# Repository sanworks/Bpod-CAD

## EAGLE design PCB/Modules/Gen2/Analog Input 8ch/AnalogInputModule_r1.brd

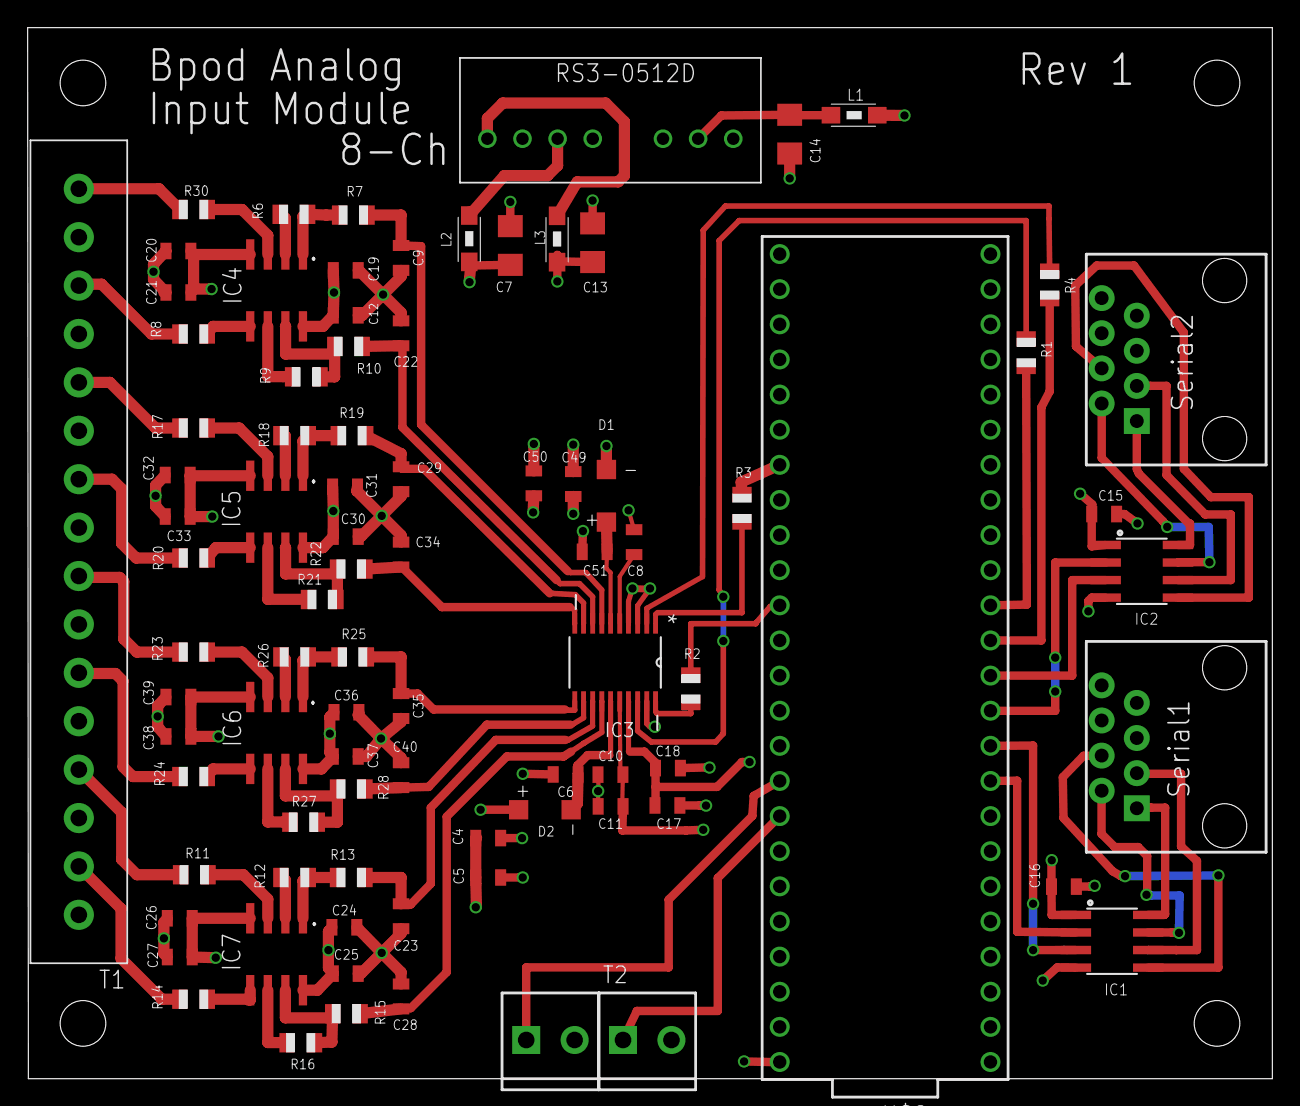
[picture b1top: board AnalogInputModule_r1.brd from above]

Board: 4 copper layers, 90.0 x 76.0 mm, 92 parts (0 on the bottom side), 74 nets.

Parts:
C4, C11, C12, C17, C21, C24, C27, C30, C33, C36, C39, C49: 10uF; 0805
C5, C6, C10, C15, C16, C18, C19, C20, C25, C26, C31, C32, C37, C38, C50, C51: 0.1uF; 0805
C7, C13, C14: 4.7uF; 1206
C8: 680nF; 0805
C9, C22, C23, C28, C29, C34, C35, C40: 2.7nF; 0805
D1, D2: MBR0520LT; SOD123
IC1, IC2: SN65HVD31DR; SO08
IC3: AD7327BRUZ; SOP65P640X120-20N
IC4, IC5, IC6, IC7: AD8599R; SO8
J9, J10: SCREWTERMINAL-3.5MM-2
L1, L2, L3: 1206
R1, R2, R3, R4: 22; R0805
R6, R8, R9, R11, R12, R14, R16, R17, R18, R20, R21, R23, R24, R26, R27, R30: 47; R0805
R7, R10, R13, R15, R19, R22, R25, R28: 180; R0805
RS3-0512D: RS3-0515D
T1: 16POS_SCREWTERMINAL
U$2, U$3: RJ45-8PTH; RJ45-8
U$4: GNDPLANESHRT
U$5, U$6, U$7, U$8: STAND-OFF
U$9: TEENSY_3.6_DIL

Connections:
+VOUT: L2.1, RS3-0512D.+VOUT
-VOUT: L3.1, RS3-0512D.-VOUT
ADC_CS: IC3.1, R3.1
AGND: C4.2, C5.2, C6.2, C8.1, C9.2, C10.2, C11.2, C12.2, C19.2, C20.2, C21.2, C22.2, C23.2, C24.2, C25.2, C26.2, C27.2, C28.2, C29.2, C30.2, C31.2, C32.2, C33.2, C34.2, C35.2, C36.2, C37.2, C38.2, C39.2, C40.2, C49.2, C50.2, C51.2, IC3.4, T1.P$1, T1.P$3, T1.P$5, T1.P$7, T1.P$9, T1.P$11, T1.P$13, T1.P$15, U$4.AGND, U$9.AGND
AIN0: R30.1, T1.P$16
AIN1: R8.1, T1.P$14
AIN2: R11.1, T1.P$4
AIN3: R14.1, T1.P$2
AIN4: R17.1, T1.P$12
AIN5: R20.1, T1.P$10
AIN6: R23.1, T1.P$8
AIN7: R24.1, T1.P$6
DGND: C7.2, C13.1, C14.2, C15.2, C16.2, C17.2, C18.2, IC1.4, IC2.4, IC3.3, IC3.19, J9.2, J10.2, RS3-0512D.-VIN, RS3-0512D.COM, U$4.GND, U$9.GND, U$9.GND1
MISO: IC3.18, R1.1
MOSI: IC3.2, R4.1
unnamed: IC1.6, U$2.3
unnamed: IC1.8, U$2.1
unnamed: IC1.5, U$2.4
unnamed: IC1.7, U$2.2
unnamed: IC2.6, U$3.3
unnamed: IC2.5, U$3.4
unnamed: IC2.8, U$3.1
unnamed: IC2.7, U$3.2
unnamed: R4.2, U$9.11
unnamed: R1.2, U$9.12
unnamed: C14.1, L1.2, RS3-0512D.+VIN
unnamed: R3.2, U$9.39/A20
unnamed: IC4.3, R30.2
unnamed: R2.2, U$9.13
unnamed: IC4.2, R6.1
unnamed: IC4.1, R6.2, R7.1
unnamed: J9.1, U$9.18/A4
unnamed: J10.1, U$9.19/A5
unnamed: IC4.5, R8.2
unnamed: IC4.6, R9.1
unnamed: IC4.7, R9.2, R10.1
unnamed: IC7.3, R11.2
unnamed: IC7.2, R12.1
unnamed: IC7.1, R12.2, R13.1
unnamed: IC7.5, R14.2
unnamed: IC7.6, R16.1
unnamed: IC7.7, R15.1, R16.2
unnamed: IC5.3, R17.2
unnamed: IC5.2, R18.1
unnamed: IC5.1, R18.2, R19.1
unnamed: IC5.5, R20.2
unnamed: IC5.6, R21.1
unnamed: IC5.7, R21.2, R22.1
unnamed: IC6.3, R23.2
unnamed: IC6.2, R26.1
unnamed: IC6.1, R25.1, R26.2
unnamed: IC6.5, R24.2
unnamed: IC6.6, R27.1
unnamed: IC6.7, R27.2, R28.1
REF: C8.2, IC3.5
RX1: IC1.2, U$9.7
RX2: IC2.2, U$9.9
SCLK: IC3.20, R2.1
TX1: IC1.3, U$9.8
TX2: IC2.3, U$9.10
V0IN: C9.1, IC3.7, R7.2
V1IN: C22.1, IC3.8, R10.2
V2IN: C28.1, IC3.14, R15.2
V3IN: C23.1, IC3.13, R13.2
V4IN: C29.1, IC3.9, R19.2
V5: C10.1, C11.1, IC3.16, L1.1, U$9.VIN
V5IN: C34.1, IC3.10, R22.2
V6IN: C40.1, IC3.12, R28.2
V7IN: C35.1, IC3.11, R25.2
V+12: C4.1, C5.1, C7.1, C12.1, C19.1, C24.1, C25.1, C30.1, C31.1, C36.1, C37.1, D2.A, IC4.8, IC5.8, IC6.8, IC7.8, L2.2
V-12: C13.2, C20.1, C21.1, C26.1, C27.1, C32.1, C33.1, C38.1, C39.1, C49.1, C50.1, D1.C, IC4.4, IC5.4, IC6.4, IC7.4, L3.2
VDD: C6.1, D2.C, IC3.15
VDRIVE: C15.1, C16.1, C17.1, C18.1, IC1.1, IC2.1, IC3.17, U$9.3.3V, U$9.3.3V3
VSS: C51.1, D1.A, IC3.6

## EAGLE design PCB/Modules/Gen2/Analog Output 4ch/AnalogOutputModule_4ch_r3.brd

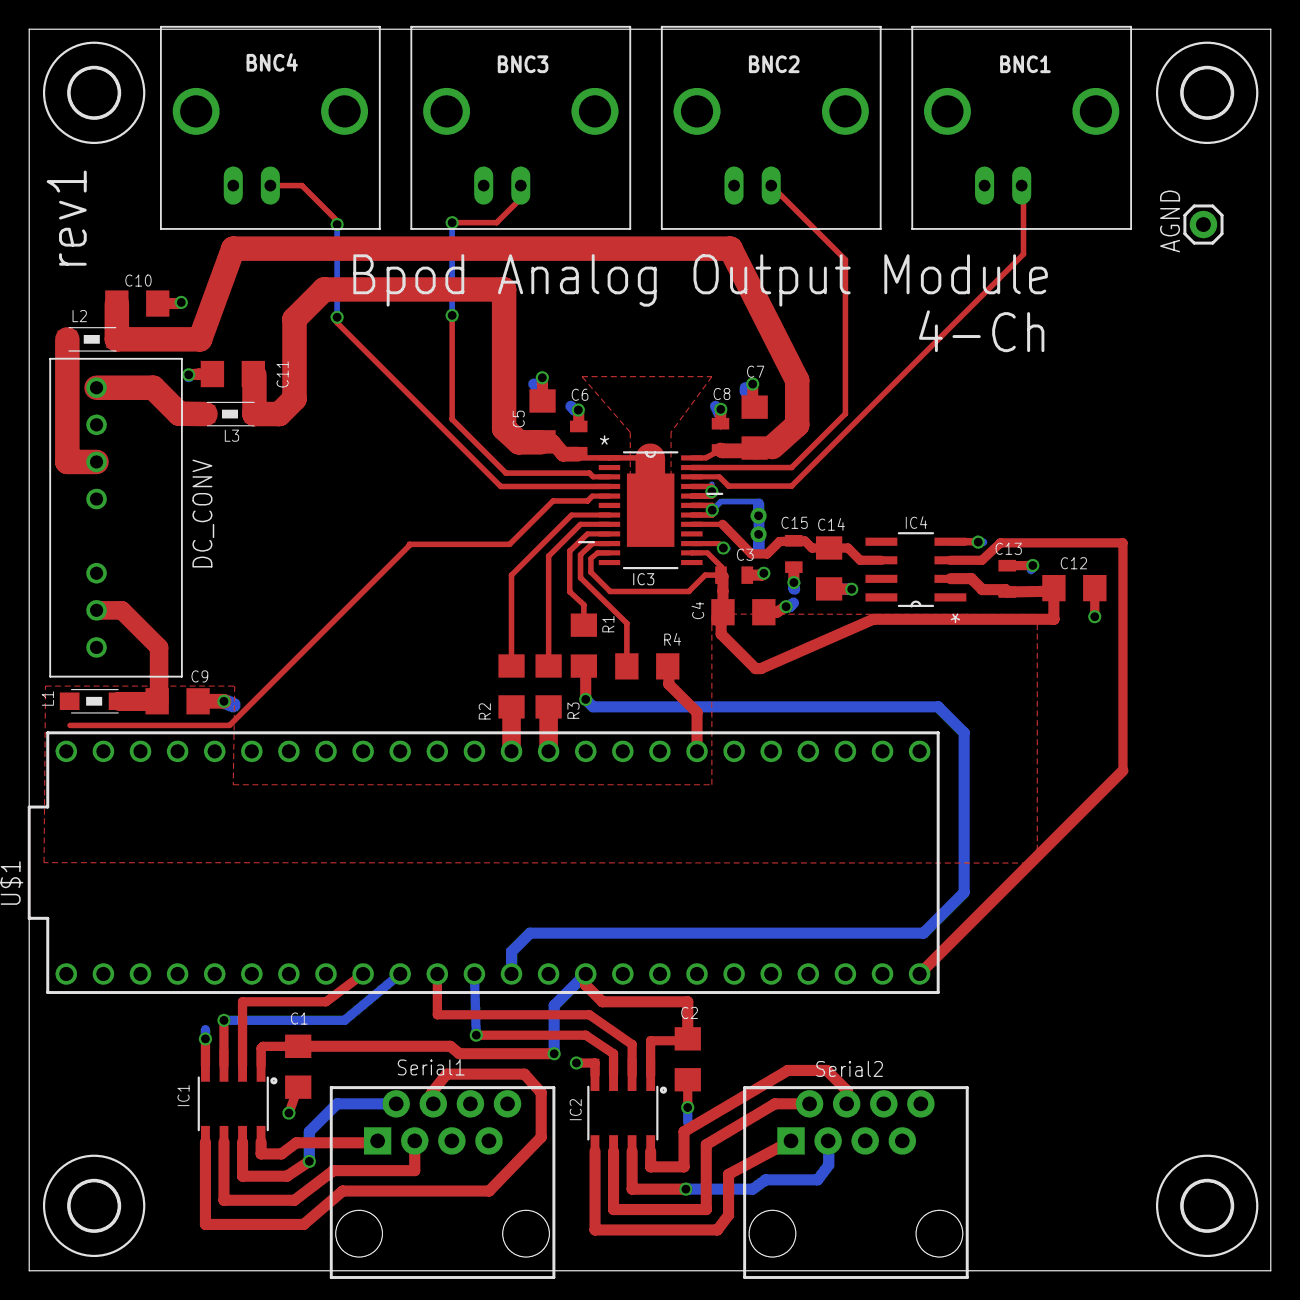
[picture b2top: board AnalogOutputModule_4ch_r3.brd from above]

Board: 2 copper layers, 85.0 x 85.0 mm, 40 parts (0 on the bottom side), 35 nets.

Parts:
AGND: 1X01
BNC1, BNC2, BNC3, BNC4: BNCPTH; BNC
C1, C2: 0.1uf; 1206@1
C3, C6, C8, C13, C15: 0.1uF; 0805
C4, C5, C7, C12: 10uf; 1206@1
C9, C10, C11: 4.7uf; 1206@1
C14: 1uf; 1206@1
DC_CONV: RS3-0515D
H1, H2, H3, H4: MOUNT-HOLE3.3; 3,3
IC1, IC2: SN65HVD31DR; SO08
IC3: AD5754RBREZ; SOP65P640X120-25N
IC4: REF193GSZ; R_8
L1, L2, L3: 1206
R1, R2, R3, R4: 22; 1206
SERIAL1, SERIAL2: RJ45-8PTH; RJ45-8
U$1: TEENSY_3.6_DIL
U$6: GNDPLANESHRT

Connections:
3VREF: C14.1, C15.1, IC3.17, IC4.6
5V: C3.2, C4.2, C12.1, C13.1, IC3.5, IC3.11, IC3.14, IC4.2, L1.1, U$1.VIN
AGND: AGND.1, BNC1.GND, BNC2.GND, BNC3.GND, BNC4.GND, C5.2, C6.2, C7.2, C8.2, C10.1, C11.2, DC_CONV.COM, IC3.18, IC3.19, IC3.20, IC3.21, U$1.AGND, U$6.AGND
GND: C1.2, C2.2, C3.1, C4.1, C9.2, C12.2, C13.2, C14.2, C15.2, DC_CONV.-VIN, IC1.4, IC2.4, IC3.15, IC4.4, U$1.GND, U$1.GND1, U$6.GND
LDAC: IC3.10, R4.1
unnamed: IC1.3, U$1.8
unnamed: IC1.2, U$1.7
unnamed: IC2.8, SERIAL2.4
unnamed: IC2.7, SERIAL2.3
unnamed: IC2.6, SERIAL2.2
unnamed: IC2.5, SERIAL2.1
unnamed: IC2.3, U$1.10
unnamed: IC2.2, U$1.9
unnamed: BNC3.S, IC3.3
unnamed: BNC4.S, IC3.4
unnamed: BNC2.S, IC3.23
unnamed: BNC1.S, IC3.22
unnamed: R1.2, U$1.11
unnamed: R3.2, U$1.13
unnamed: DC_CONV.-VOUT, L3.1
unnamed: DC_CONV.+VOUT, L2.1
unnamed: R2.2, U$1.14/A0
unnamed: R4.2, U$1.39/A20
unnamed: IC1.8, SERIAL1.1
unnamed: IC1.7, SERIAL1.2
unnamed: IC1.6, SERIAL1.3
unnamed: IC1.5, SERIAL1.4
unnamed: C7.1, C8.1, C10.2, IC3.24, L2.2
unnamed: C9.1, DC_CONV.+VIN, L1.2
REF_ENABLE: IC4.3, U$1.32/A13
SCK0: IC3.8, R3.1
SDA0: IC3.9, R1.1
SYNC: IC3.7, R2.1
VCC: C1.1, C2.1, IC1.1, IC2.1, U$1.3.3V, U$1.3.3V3
VSS: C5.1, C6.1, C11.1, IC3.1, IC3.25, L3.2

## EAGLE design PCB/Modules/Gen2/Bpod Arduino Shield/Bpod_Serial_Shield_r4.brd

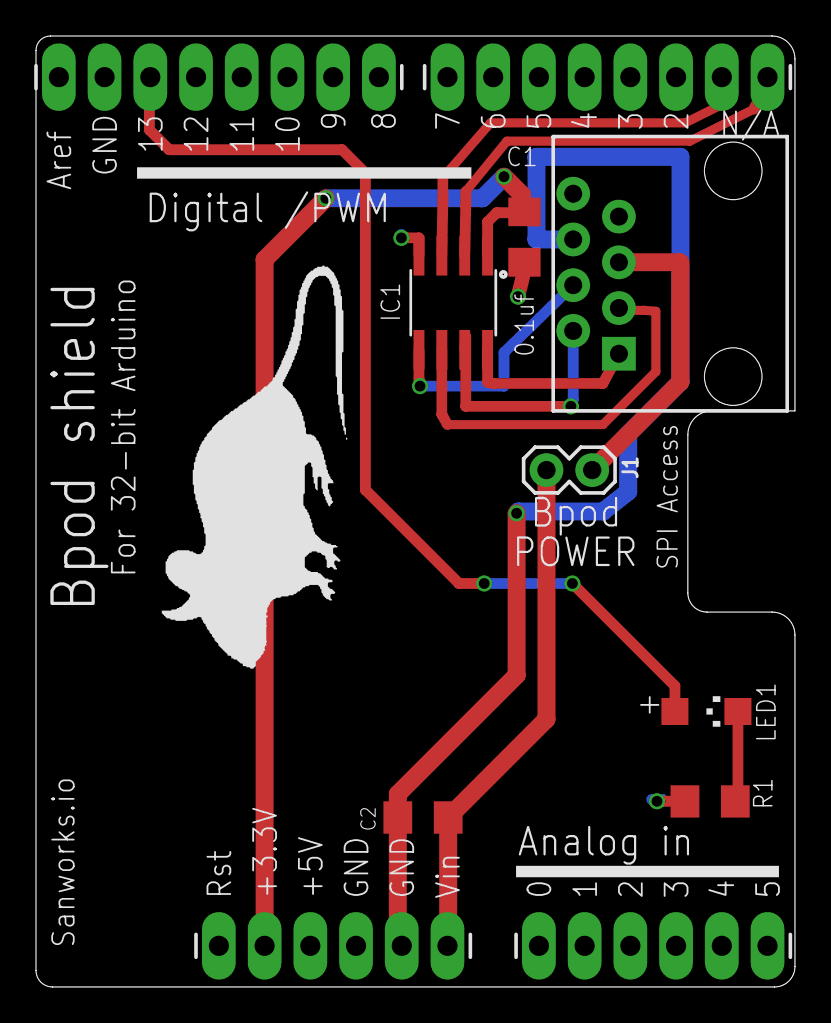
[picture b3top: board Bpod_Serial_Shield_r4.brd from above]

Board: 2 copper layers, 42.2 x 52.8 mm, 12 parts (0 on the bottom side), 13 nets.

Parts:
ALG: 1X06_LONGPADS
C1: 1206
C2: 0.1uf; 1206
DIGI1, DIGI2: 1X08_LONGPADS
IC1: SN65HVD31DR; SO08
J1: 1X02
LED1: CHIPLED_1206
PWR: 1X06_LONGPADS
R1: 56; 1206
U$1: RJ45-8PTH; RJ45-8
U$2: MOUSELOGO

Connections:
GND: C1.2, IC1.4, PWR.4, R1.1
unnamed: C1.1, IC1.1, PWR.2
unnamed: LED1.C, R1.2
unnamed: DIGI2.3, LED1.A
unnamed: DIGI1.7, IC1.3
unnamed: C2.1, J1.2, PWR.6
unnamed: DIGI1.8, IC1.2
unnamed: IC1.8, U$1.1
unnamed: IC1.7, U$1.2
unnamed: IC1.6, U$1.3
unnamed: IC1.5, U$1.4
unnamed: C2.2, PWR.5, U$1.6
unnamed: J1.1, U$1.5

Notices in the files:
parts and their libraries:
SparkFun-Capacitors: Licensing: Creative Commons ShareAlike 4.0 International - https://creativecommons.org/licenses/by-sa/4.0
SparkFun: Licensing: CC v3.0 Share-Alike You are welcome to use this library for commercial purposes.
